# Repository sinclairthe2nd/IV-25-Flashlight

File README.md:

# IV-25-Flashlight
This is the Code that is used for the IV-25 Battery Indicator Torch that im building

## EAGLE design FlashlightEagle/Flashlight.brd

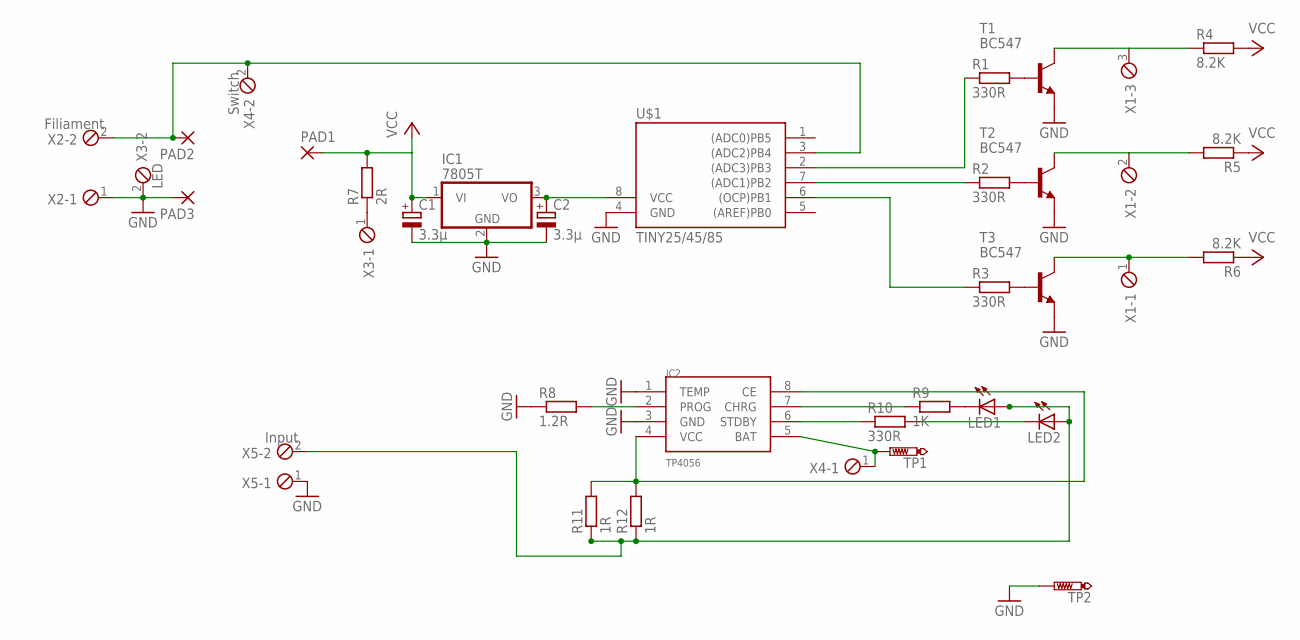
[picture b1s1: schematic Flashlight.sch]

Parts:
C1, C2: 3.3µ; E2,5-6
IC1: 7805T; TO220H
IC2: TP4056; SOP-8
LED1, LED2: LED3MM
PAD1, PAD2, PAD3: 3,81/1,3
R1, R2, R3: 330R; R1206
R4, R5, R6: 8.2K; R1206
R7: 2R; 0411/12
R8: 1.2R; M1206
R9: 1K; M1206
R10: 330R; M1206
R11, R12: 1R; M1206
T1, T2, T3: BC547; TO92
TP1, TP2: PTR1PAD1-13; P1-13
U$1: TINY25/45/85; DIL08
X1: MPT3; 3POL254
X2: Filiament; 2POL254
X3: LED; 2POL254
X4: Switch; 2POL254
X5: Input; 2POL254

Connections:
GND: C1.-, C2.-, IC1.2 (GND), IC2.1 (TEMP), IC2.3 (GND), PAD3.1, R8.1, T1.1 (E), T2.1 (E), T3.1 (E), TP2.TP, U$1.4 (GND), X2.1, X3.2, X5.1
unnamed: R1.2, T1.2 (B)
unnamed: R2.2, T2.2 (B)
unnamed: R3.2, T3.2 (B)
unnamed: R4.1, T1.3 (C), X1.3
unnamed: R5.2, T2.3 (C), X1.2
unnamed: R6.2, T3.3 (C), X1.1
unnamed: PAD2.1, U$1.3 ((ADC2)PB4), X2.2, X4.2
unnamed: R7.1, X3.1
unnamed: IC2.7 (CHRG), R9.1
unnamed: R3.1, U$1.6 ((OCP)PB1)
unnamed: R2.1, U$1.7 ((ADC1)PB2)
unnamed: R1.1, U$1.2 ((ADC3)PB3)
unnamed: C2.+, IC1.3 (VO), U$1.8 (VCC)
unnamed: IC2.6 (STDBY), R10.1
unnamed: IC2.2 (PROG), R8.2
unnamed: IC2.4 (VCC), IC2.8 (CE), R11.2, R12.2
unnamed: IC2.5 (BAT), TP1.TP, X4.1
unnamed: LED1.K (C), R9.2
unnamed: LED2.K (C), R10.2
unnamed: LED1.A, LED2.A, R11.1, R12.1, X5.2
VCC: C1.+, IC1.1 (VI), PAD1.1, R4.2, R5.1, R6.1, R7.2

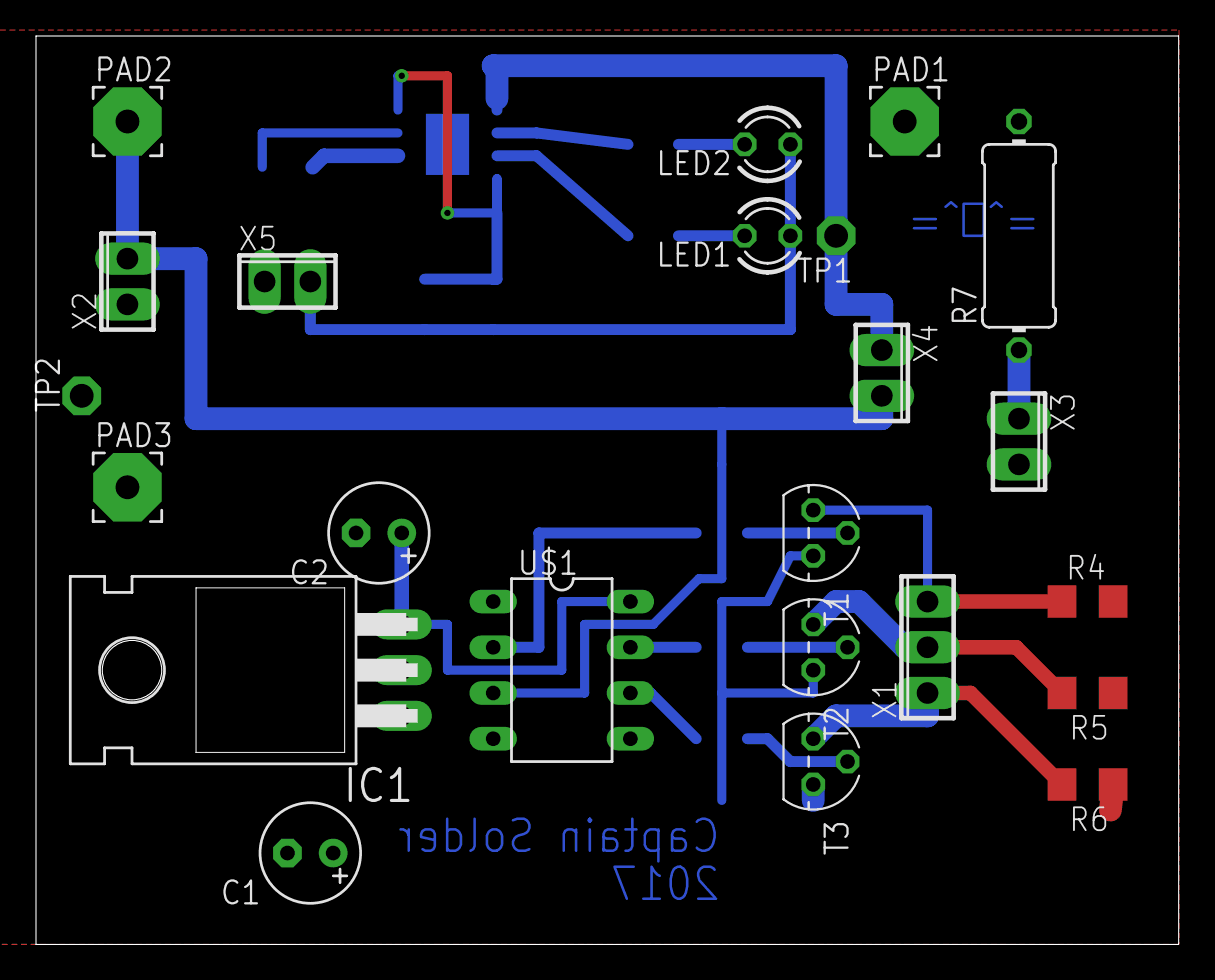
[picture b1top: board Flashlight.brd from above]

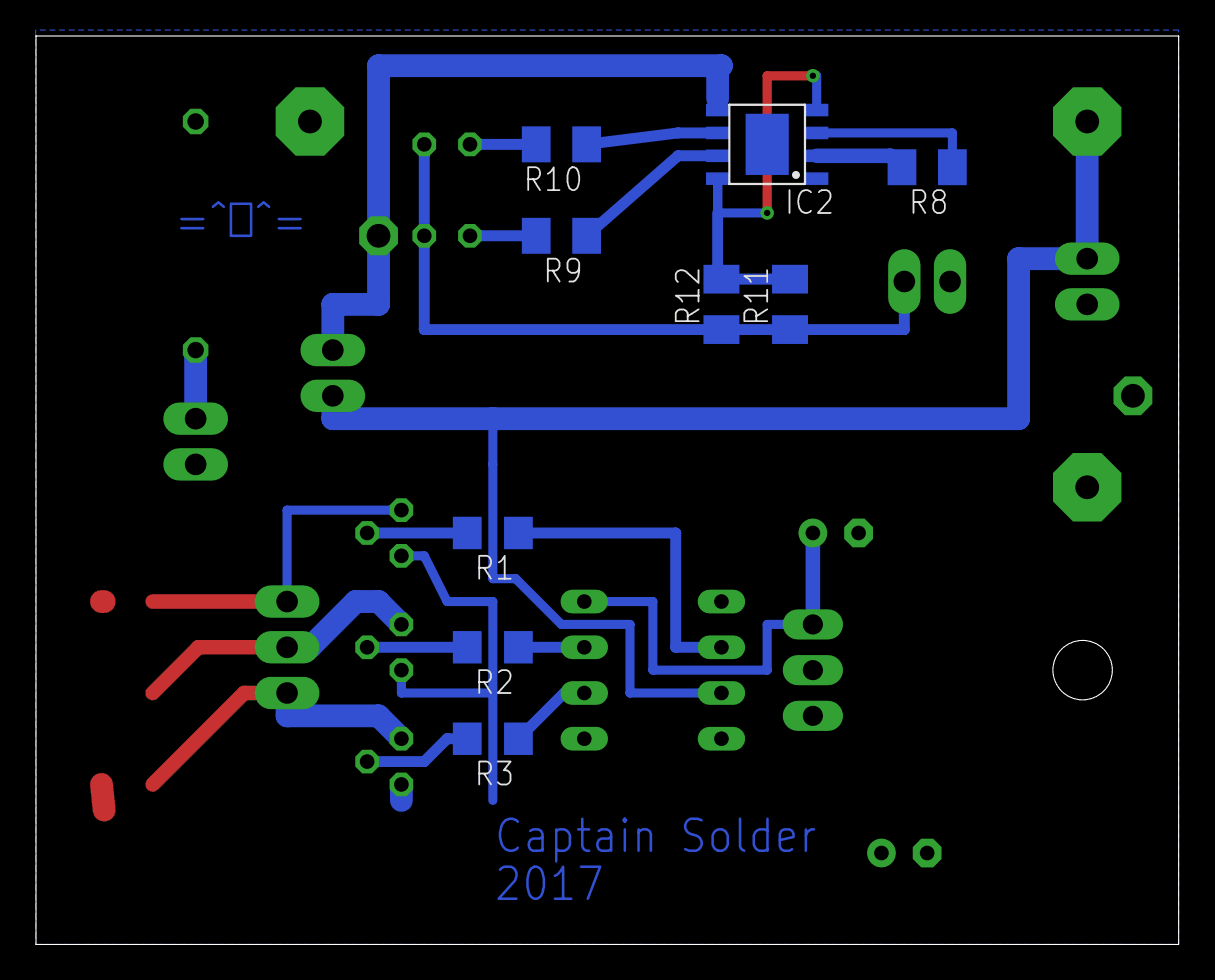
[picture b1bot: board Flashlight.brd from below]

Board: 2 copper layers, 63.5 x 50.5 mm, 32 parts (9 on the bottom side), 22 nets.

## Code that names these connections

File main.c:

#include <avr/io.h>
#include <util/delay.h>
void initADC()
{
  /* this function initialises the ADC 

        ADC Prescaler Notes:
	--------------------

	   ADC Prescaler needs to be set so that the ADC input frequency is between 50 - 200kHz.
  
           For more information, see table 17.5 "ADC Prescaler Selections" in 
           chapter 17.13.2 "ADCSRA – ADC Control and Status Register A"
          (pages 140 and 141 on the complete ATtiny25/45/85 datasheet, Rev. 2586M–AVR–07/10)

           Valid prescaler values for various clock speeds
	
	     Clock   Available prescaler values
           ---------------------------------------
             1 MHz   8 (125kHz), 16 (62.5kHz)
             4 MHz   32 (125kHz), 64 (62.5kHz)
             8 MHz   64 (125kHz), 128 (62.5kHz)
            16 MHz   128 (125kHz)

           Below example set prescaler to 128 for mcu running at 8MHz
           (check the datasheet for the proper bit values to set the prescaler)
  */
  //Guuddygit
  // 8-bit resolution
  // set ADLAR to 1 to enable the Left-shift result (only bits ADC9..ADC2 are available)
  // then, only reading ADCH is sufficient for 8-bit results (256 values)
  
  ADMUX =
            (1 << ADLAR) |     // left shift result
            (0 << REFS1) |     // Sets ref. voltage to VCC, bit 1
            (0 << REFS0) |     // Sets ref. voltage to VCC, bit 0
            (0 << MUX3)  |     // use ADC2 for input (PB4), MUX bit 3
            (0 << MUX2)  |     // use ADC2 for input (PB4), MUX bit 2
            (1 << MUX1)  |     // use ADC2 for input (PB4), MUX bit 1
            (0 << MUX0);       // use ADC2 for input (PB4), MUX bit 0

  ADCSRA = 
            (1 << ADEN)  |     // Enable ADC 
            (1 << ADPS2) |     // set prescaler to 64, bit 2 
            (1 << ADPS1) |     // set prescaler to 64, bit 1 
            (0 << ADPS0);      // set prescaler to 64, bit 0  
}

int main(void) 
{
DDRB = 0b00001111; //Set Data Direction Register so PB 0,1,2,3 are outputs while  Pb 4 is an Input
  
  initADC();

  while(1)
  {
 // take 100x 8-bit samples and calculate a rolling average of the last 15 samples
  
 float voltage_fl;        // real battery voltage (0-5V) with decimals
 float adc_step=0.01953;  // (0-5V over 256 values)
 int sample_loop;

 for (sample_loop=100; sample_loop > 0 ; sample_loop --)
 {

   ADCSRA |= (1 << ADSC);         // start ADC measurement
   while (ADCSRA & (1 << ADSC) ); // wait till conversion complete 

   voltage_fl = voltage_fl + (((ADCH * adc_step) - voltage_fl) / 15);  // integrated last 15-sample rolling average

 }

 
    if (voltage_fl > 3.7) // Close to Full at 1C load; Topmost Segment
    {      
			PORTB &= ~(1 << PB1); // PB1 goes low 
    } 
    else 
    {
    		PORTB |= (1 << PB1); // PB1 goes high  
    }

     if (voltage_fl > 3.5) // Middle Segment
    {      
			PORTB &= ~(1 << PB2); // PB2 goes low
    }
    else 
    {
			PORTB |= (1 << PB2); // PB2 goes high 
    } 
     
    if (voltage_fl > 3.3) // Bottomost Segment
    { 
			PORTB |= (1 << PB3); // PB3 goes high
    }
    else
    {		
		PORTB &= ~(1 << PB3); // PB3 goes low
    }
        
    if (voltage_fl < 3.0) // Blink
    {
		PORTB &= ~(1 << PB3); // PB3 goes low
		_delay_ms(50);
		PORTB |= (1 << PB3); // PB3 goes high
		_delay_ms(50);
     }
     else 
     {
		PORTB &= ~(1 << PB3); // PB3 goes low
	 }
     
    //Fin
   
  }

  return 0;
}

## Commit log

2018-05-08 On branch batterymanagement
